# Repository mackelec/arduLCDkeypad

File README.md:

# arduLCDkeypad

- Designed to reduce the workload and pin count required to incorporate a LCD and keypad.  Pease copy and improve this project in any way you wish.

## Hardware
- ATmega328 based LCD piggy back board with 5x4 Keypad port.
- ATmega328 using internal 8Mhz clock.
- uses MCUdude Minicore bootloader.
- Arduino source code.
- Piggyback for standard LCD up to 20x4 LCD.
- Serial and I2c interface.
- Variable contrast control.
- Variable Backlight control.
- Piezo, click sound on key press.

## Firmware
- Communicate Commands by either 9600 serial or I2c (address 42).
- Basic LCD fuctions like Clear, Cursor, Print, Print at,
### Extra features
- Predefine a field (template) with a format string (as in C printf format).  Just update a variable value and it will format and print it at the right location.
- Handles Float Formats (basic).  eg., "%03.5f"
- Predefined Time formats.  ("HH:mm:ss") or ("YYYY-MM-dd HH:mm:ss") Using the long value (time_t ) as the variable type.
- Auto time mode: using Time library to maintain a real time clock; if used it will autonomously refresh the time field every second.
- Dual settings for backlight level.  Keypress activates higher backlight level and times out to lower level.

## Library
- Simple interfacing to arduLCDkeypad.

### Commands

- arduLCDkeypad(Serial) 
- arduLCDkeypad(Wire,42)   
Instantiation of arduLCDkeypad object.  If Wire, second parameter defines I2C address.

- Clear()    
Clears LCD
- setCursor(col,row)   
- printAt(char message[],col,row,blank)      
Prints a char string at col,row. Blank is optional; Blank will print number (blank value) of spaces at col,row before printing string.
- Contrast( int percent)     
Sets the contrast level (0 - 100 default is 5).
- BackLight(int percentStandby, int percentActive)      
Set the Backlight brightness.  When key is pressed it goes to Active level, when BackLight Timer times out it goes back to standby level.
- BackLightTimer(int backlightTimeout)    
Sets the backlightTimer (seconds)
- Buzz(int BuzzLen)    
Turns buzzer on for buzzLen milliseconds (one shot)
- char keyPressed()   
Returns a char value of a keypress.  A value of NO_KEY indicates no key was pressed
- bool recReset()   
returns True if arduLCDkeyboard has been RESET. Must be called after calling keyPressed().
- bool present()    
returns true if arduLCDkeyboard is responding.  Must be called after calling keyPressed().
- updateLcdField(id,col,row,len,visible,strFormat)    
LCD fields are available to preset a field, which has its position and format string (C standard) stored, then only needing the value for that field to be updated as required.  That value will be displayed using the format string.
- updateLcdFieldFormat(id,char strFormat)    
Updates the Format stored for the field.  This function is useful because the standard WIRE library only has a buffer of 34 and a long format string can cause the updateLcdField command to exceed the buffer size.
- updateTime(unsigned long notTime)     
ArduLCDkeyboard uses Time library to keep real time.  Use time_t (which is unsigned long) to update to current time.
- setAutoTime(fieldId)   
This allows arduLCDkeypad to maintain the LCD field automatically (on a second basis).  You need to prime the LCD field with a suitable format string ie, "HH:mm:ss" or "YYYY-MM-dd HH:mm:ss". Negative Id will turn it off.

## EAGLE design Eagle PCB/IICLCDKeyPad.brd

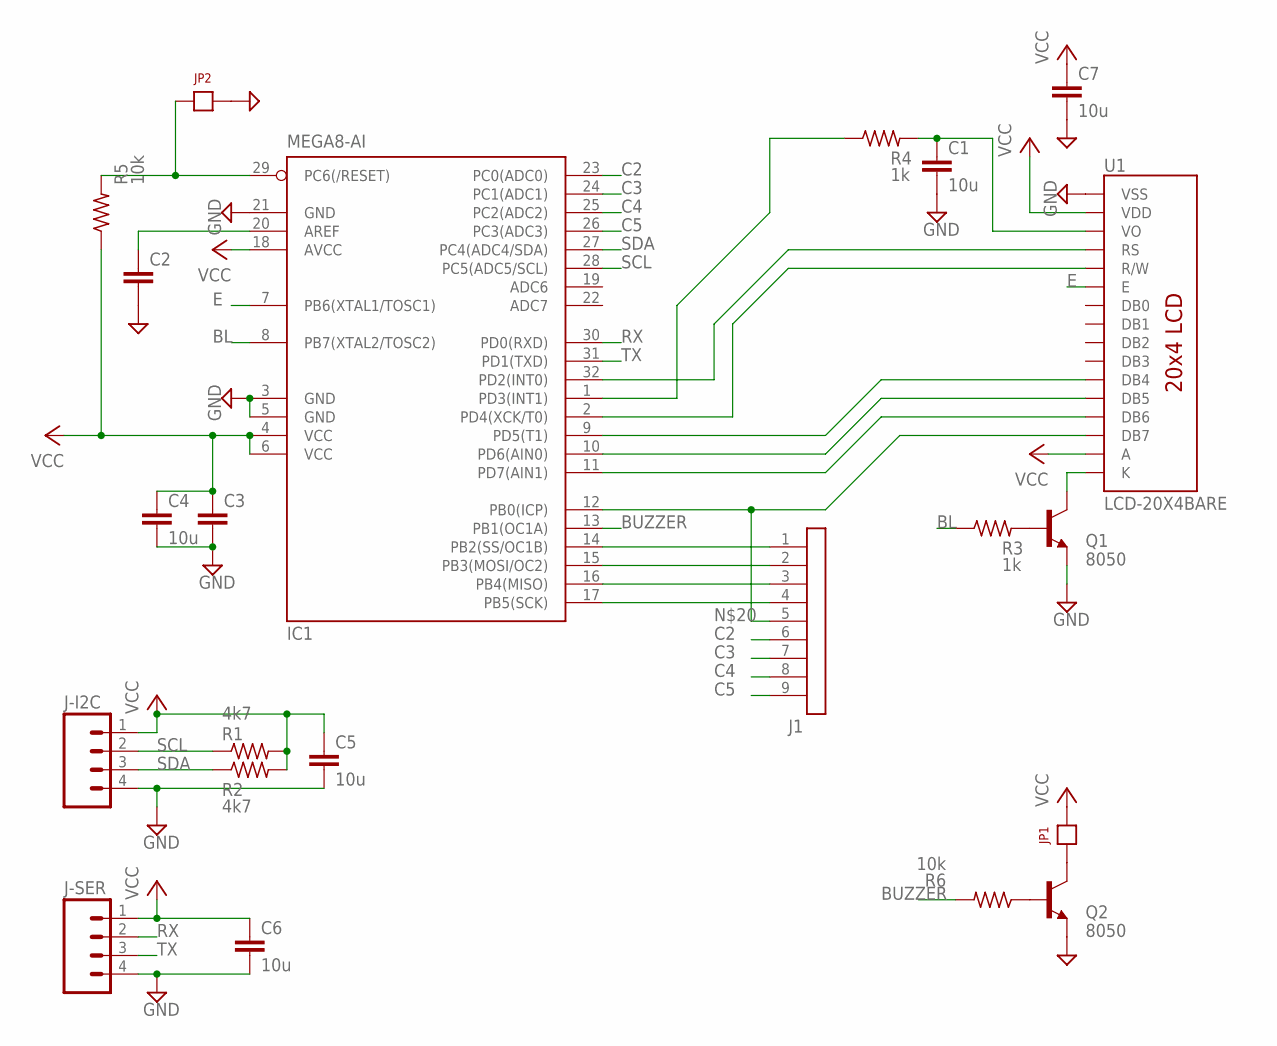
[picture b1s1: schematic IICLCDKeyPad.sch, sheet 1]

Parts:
C1, C4, C5, C6, C7: 10u; 0805
C2, C3: CAP0603-CAP; 0603-CAP
IC1: MEGA8-AI; TQFP32-08; MPN ATMEGA8-16AU
J1: SIL-9
J-I2C: MO4POL; MOLEX-4
J-SER: MO4POL; MOLEX-4
JP1, JP2: JP1
Q1, Q2: 8050; SOT23-BEC
R1, R2: 4k7; R0603
R3, R4: 1k; R0603
R5, R6: 10k; R0603
U1: LCD-20X4BARE; LCD-16X2_BARE

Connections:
BL: IC1.8 (PB7(XTAL2/TOSC2)), R3.1
BUZZER: IC1.13 (PB1(OC1A)), R6.2
C2: IC1.23 (PC0(ADC0)), J1.6
C3: IC1.24 (PC1(ADC1)), J1.7
C4: IC1.25 (PC2(ADC2)), J1.8
C5: IC1.26 (PC3(ADC3)), J1.9
D6: IC1.11 (PD7(AIN1)), U1.13 (DB6)
E: IC1.7 (PB6(XTAL1/TOSC1)), U1.6 (E)
GND: C1.2, C2.2, C3.2, C4.2, C5.2, C6.2, C7.2, IC1.3 (GND), IC1.5 (GND), IC1.21 (GND), J-I2C.4, J-SER.4, JP2.2, Q1.E, Q2.E, U1.1 (VSS)
unnamed: IC1.14 (PB2(SS/OC1B)), J1.1
unnamed: Q1.C, U1.16 (K)
unnamed: Q1.B, R3.2
unnamed: C1.1, R4.2, U1.3 (VO)
unnamed: IC1.9 (PD5(T1)), U1.11 (DB4)
unnamed: C2.1, IC1.20 (AREF)
unnamed: IC1.10 (PD6(AIN0)), U1.12 (DB5)
unnamed: IC1.1 (PD3(INT1)), R4.1
unnamed: IC1.32 (PD2(INT0)), U1.4 (RS)
unnamed: JP1.1, Q2.C
unnamed: Q2.B, R6.1
unnamed: IC1.2 (PD4(XCK/T0)), U1.5 (R/W)
unnamed: IC1.15 (PB3(MOSI/OC2)), J1.2
unnamed: IC1.29 (PC6(/RESET)), JP2.1, R5.2
unnamed: IC1.16 (PB4(MISO)), J1.3
unnamed: IC1.17 (PB5(SCK)), J1.4
unnamed: IC1.12 (PB0(ICP)), J1.5, U1.14 (DB7)
RX: IC1.30 (PD0(RXD)), J-SER.2
SCL: IC1.28 (PC5(ADC5/SCL)), J-I2C.2, R1.1
SDA: IC1.27 (PC4(ADC4/SDA)), J-I2C.3, R2.1
TX: IC1.31 (PD1(TXD)), J-SER.3
VCC: C3.1, C4.1, C5.1, C6.1, C7.1, IC1.4 (VCC), IC1.6 (VCC), IC1.18 (AVCC), J-I2C.1, J-SER.1, JP1.2, R1.2, R2.2, R5.1, U1.2 (VDD), U1.15 (A)

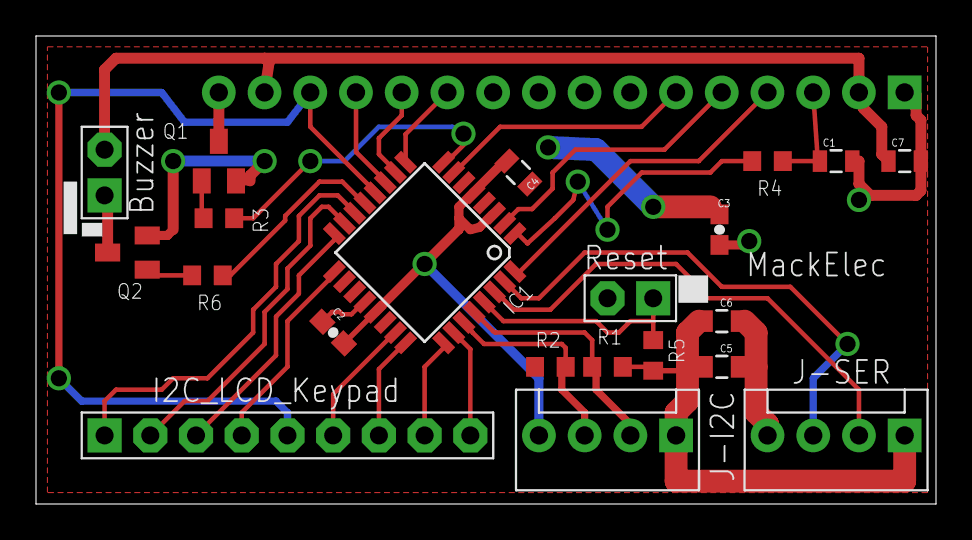
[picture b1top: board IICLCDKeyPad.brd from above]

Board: 2 copper layers, 50.0 x 26.0 mm, 22 parts (1 on the bottom side), 31 nets.

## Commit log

2017-10-11 Create note
2017-10-27 Create SRC_Library
2017-10-28 Create Libraries
2017-10-28 Create Libraries Used
2017-10-28 Create junk

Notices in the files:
parts and their libraries:
SparkFun-Passives: Licensing: CC v3.0 Share-Alike You are welcome to use this library for commercial purposes.
